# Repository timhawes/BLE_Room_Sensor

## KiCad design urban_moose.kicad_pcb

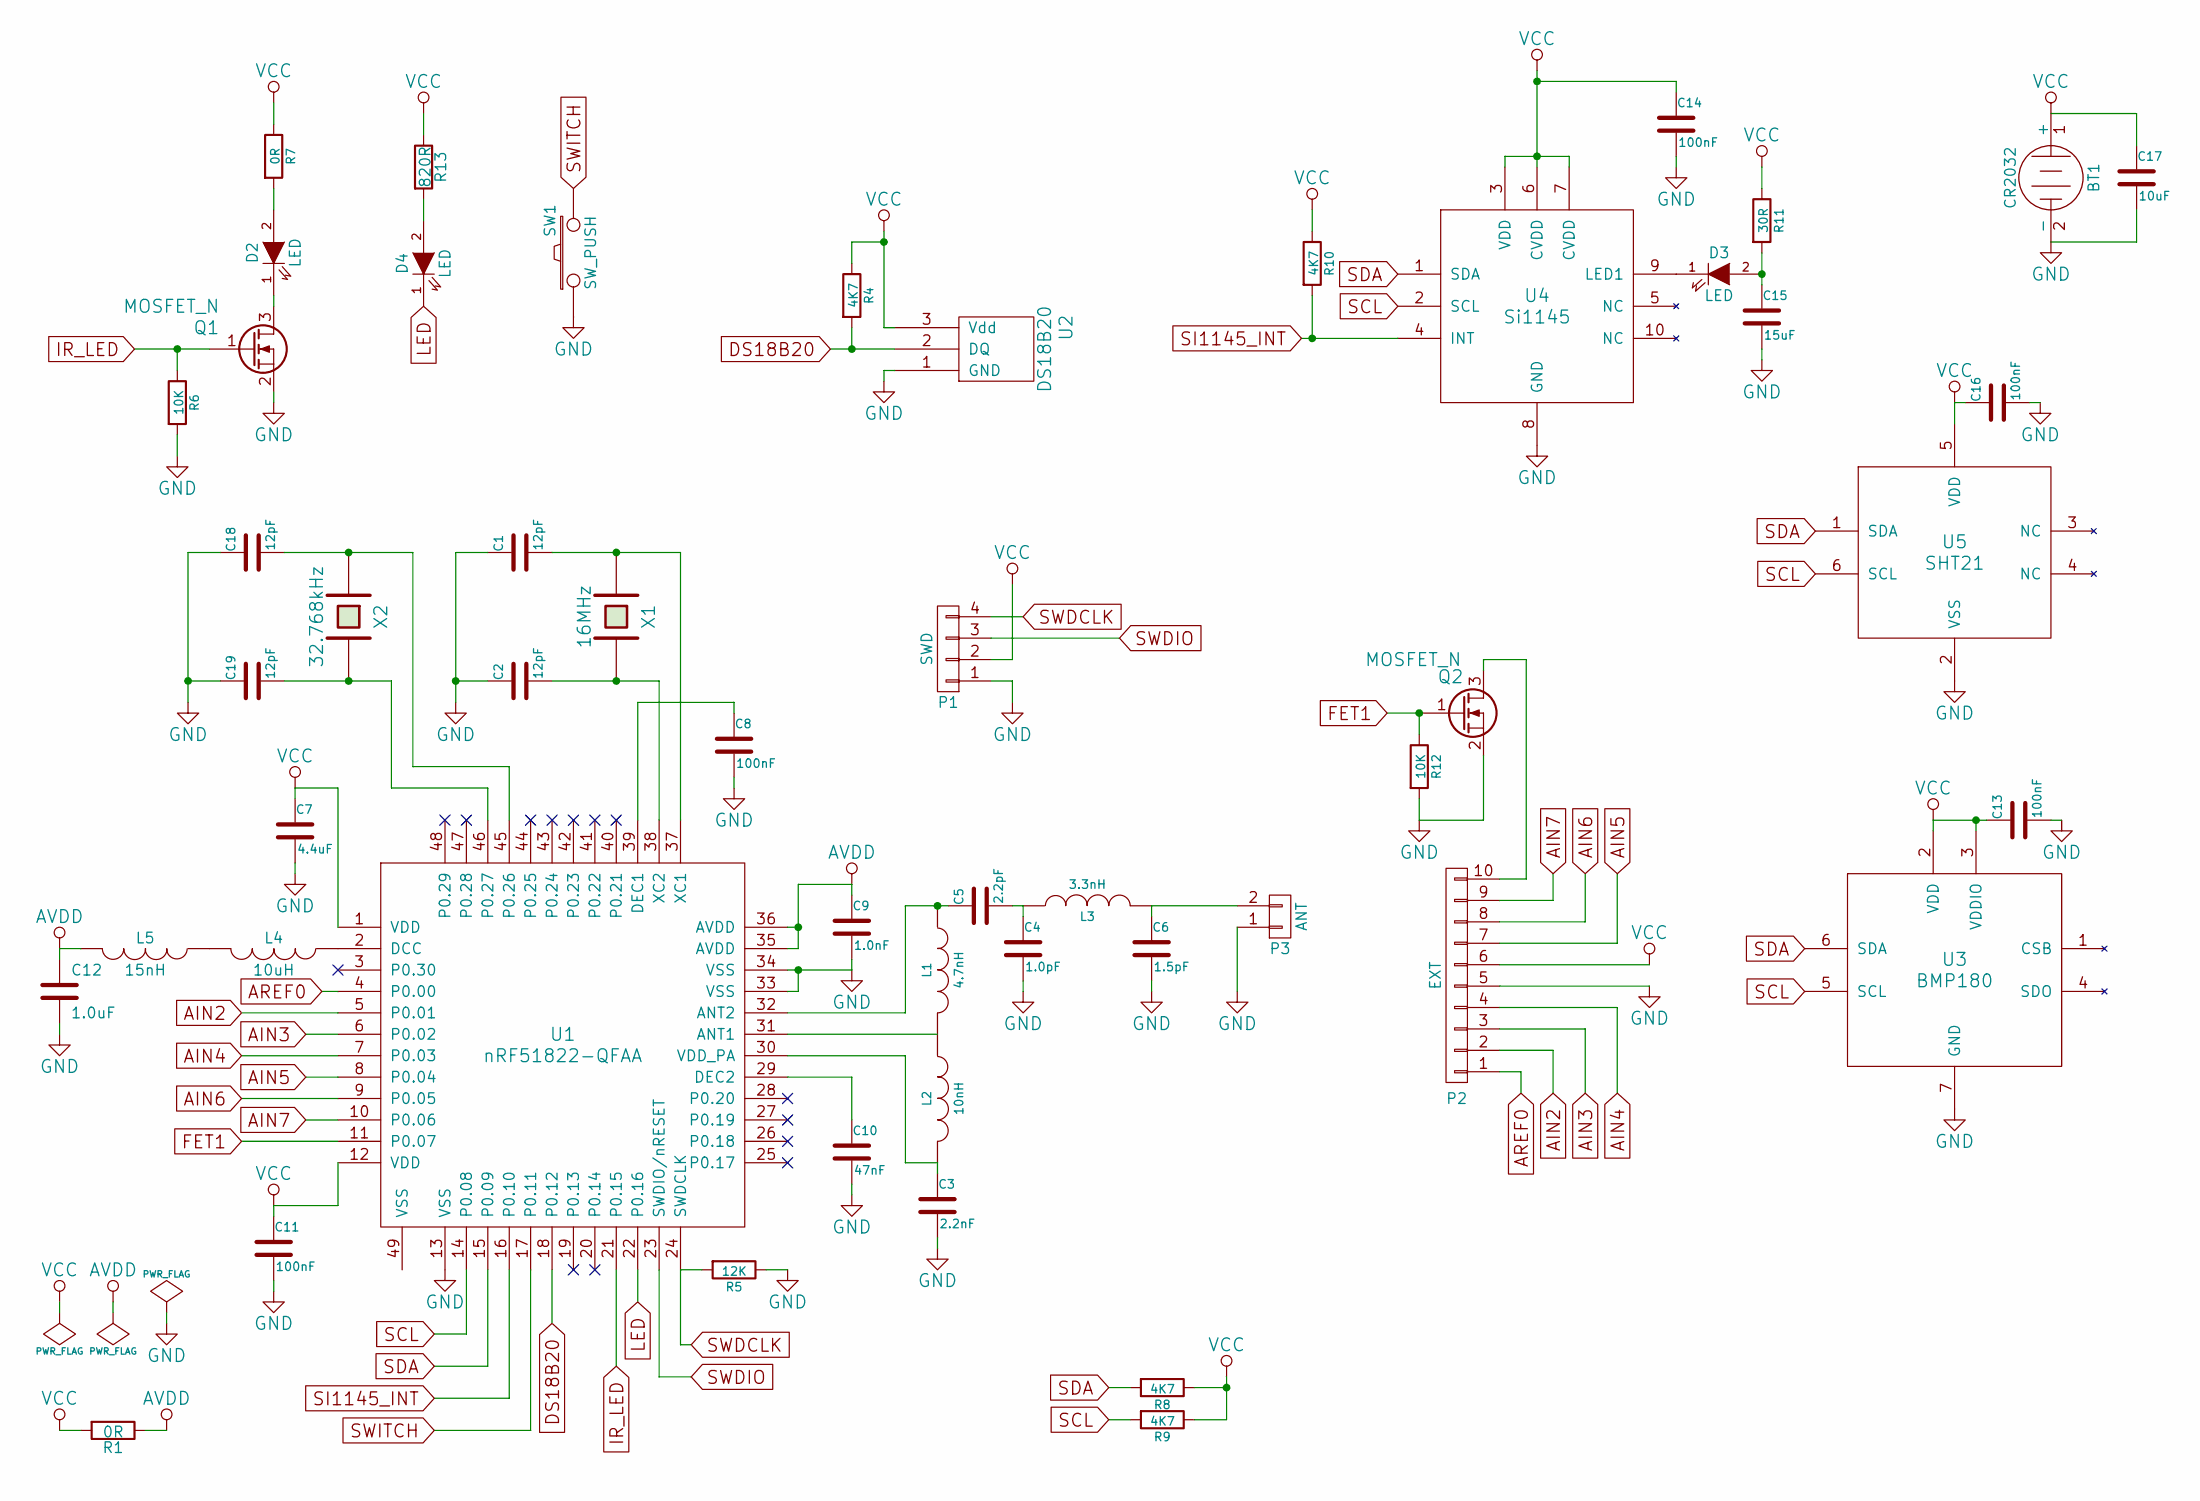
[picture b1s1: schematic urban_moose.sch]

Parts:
BT1: CR2032; BAT-HLD-001
C1, C2, C18, C19: 12pF; C_0402
C3: 2.2nF; C_0402
C4: 1.0pF; C_0402
C5: 2.2pF; C_0402
C6: 1.5pF; C_0402
C7: 4.4uF; C_0603
C8, C11, C13, C14, C16: 100nF; C_0402
C9: 1.0nF; C_0402
C10: 47nF; C_0402
C12: 1.0uF; C_0603
C15: 15uF; C_1206
C17: 10uF; C_1206
D2, D3, D4: LED; LED-0603
L1: 4.7nH; R_0402
L2: 10nH; R_0402
L3: 3.3nH; R_0402
L4: 10uH; R_0603
L5: 15nH; R_0402
P1: SWD; Pin_Header_Straight_1x04
P2: EXT; Pin_Header_Straight_1x10
P3: ANT; ANT-2.4GHz
Q1, Q2: MOSFET_N; SOT-23
R1, R7: 0R; R_0402
R4, R8, R9, R10: 4K7; R_0402
R5: 12K; R_0402
R6, R12: 10K; R_0402
R11: 30R; R_0402
R13: 820R; R_0402
SW1: SW_PUSH; EVQPT5
U1: nRF51822-QFAA; UQFN-48-1EP_6x6mm_Pitch0.4mm
U2: DS18B20; Pin_Header_Straight_1x03
U3: BMP180
U4: Si1145; Si114x
U5: SHT21
X1: 16MHz; CX2520DB
X2: 32.768kHz; FC-135

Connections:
AIN2: P2.2, U1.5 (P0.01)
AIN3: P2.3, U1.6 (P0.02)
AIN4: P2.4, U1.7 (P0.03)
AIN5: P2.7, U1.8 (P0.04)
AIN6: P2.8, U1.9 (P0.05)
AIN7: P2.9, U1.10 (P0.06)
AREF0: P2.1, U1.4 (P0.00)
AVDD: C9.1, C12.1, L5.2, R1.1, U1.35 (AVDD), U1.36 (AVDD)
DS18B20: R4.2, U1.18 (P0.12), U2.2 (DQ)
FET1: Q2.1 (G), R12.1, U1.11 (P0.07)
GND: BT1.2 (-), C1.1, C2.1, C3.2, C4.2, C6.2, C7.2, C8.2, C9.2, C10.2, C11.2, C12.2, C13.2, C14.2, C15.2, C16.2, C17.2, C18.1, C19.1, P1.1, P2.5, P3.1, Q1.2 (S), Q2.2 (S), R5.1, R6.2, R12.2, SW1.1, U1.13 (VSS), U1.33 (VSS), U1.34 (VSS), U1.49 (VSS), U2.1 (GND), U3.7 (GND), U4.8 (GND), U5.2 (VSS)
IR_LED: Q1.1 (G), R6.1, U1.21 (P0.15)
LED: D4.1 (K), U1.22 (P0.16)
unnamed: C1.2, U1.37 (XC1), X1.1
unnamed: C2.2, U1.38 (XC2), X1.2
unnamed: C3.1, L2.2, U1.30 (VDD_PA)
unnamed: C4.1, C5.2, L3.1
unnamed: C5.1, L1.1, U1.32 (ANT2)
unnamed: C6.1, L3.2, P3.2
unnamed: C8.1, U1.39 (DEC1)
unnamed: C10.1, U1.29 (DEC2)
unnamed: C15.1, D3.2 (A), R11.2
unnamed: C18.2, U1.45 (P0.26), X2.1
unnamed: C19.2, U1.46 (P0.27), X2.2
unnamed: D2.1 (K), Q1.3 (D)
unnamed: D2.2 (A), R7.2
unnamed: D3.1 (K), U4.9 (LED1)
unnamed: D4.2 (A), R13.2
unnamed: L1.2, L2.1, U1.31 (ANT1)
unnamed: L4.1, U1.2 (DCC)
unnamed: L4.2, L5.1
unnamed: P2.10, Q2.3 (D)
SCL: R9.2, U1.14 (P0.08), U3.5 (SCL), U4.2 (SCL), U5.6 (SCL)
SDA: R8.2, U1.15 (P0.09), U3.6 (SDA), U4.1 (SDA), U5.1 (SDA)
SI1145_INT: R10.2, U1.16 (P0.10), U4.4 (INT)
SWDCLK: P1.4, R5.2, U1.24 (SWDCLK)
SWDIO: P1.3, U1.23 (SWDIO/nRESET)
SWITCH: SW1.2, U1.17 (P0.11)
VCC: BT1.1 (+), C7.1, C11.1, C13.1, C14.1, C16.1, C17.1, P1.2, P2.6, R1.2, R4.1, R7.1, R8.1, R9.1, R10.1, R11.1, R13.1, U1.1 (VDD), U1.12 (VDD), U2.3 (Vdd), U3.2 (VDD), U3.3 (VDDIO), U4.3 (VDD), U4.6 (CVDD), U4.7 (CVDD), U5.5 (VDD)

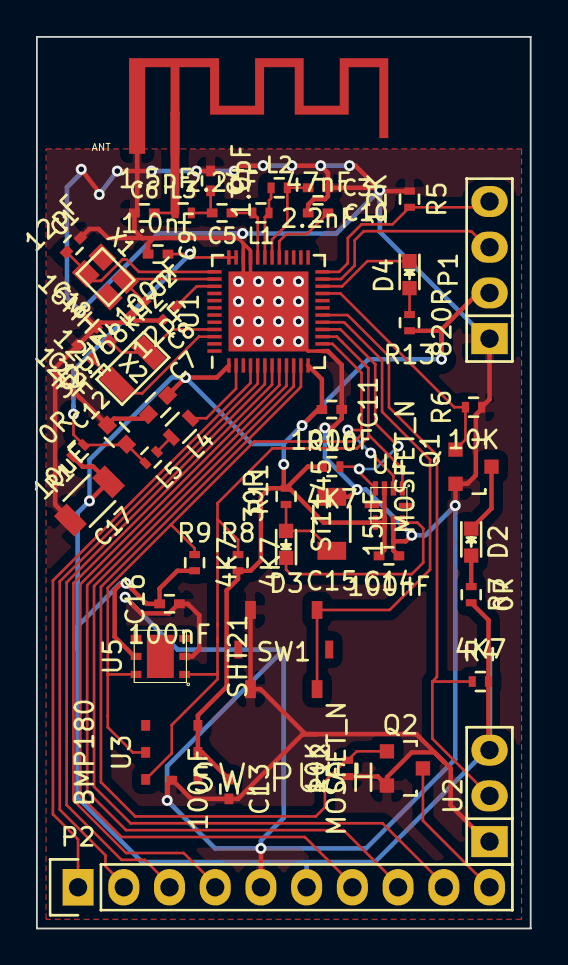
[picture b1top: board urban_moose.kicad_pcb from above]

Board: 2 copper layers, 27.4 x 49.5 mm, 52 parts (1 on the bottom side), 39 nets.

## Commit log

2015-01-15 Initial commit.
2015-01-17 Multiple changes.
    DC/DC mode support
    LF crystal support
    RGB LED replaced with simple LED
2015-05-24 Many rolled-up changes
2015-05-24 Project renamed
2015-05-24 Ground vias added near matching components
2015-05-30 Tidy-ups
2015-05-30 Gerbers generated
2015-05-30 Move antenna away from ground plane
2015-05-31 Made some references smaller. Generated paste layers.
2015-06-10 Remove paste from battery contact
2015-06-10 .gitignore file added
2015-06-10 Gerbers regenerated, and new file extensions used
2015-11-04 Fixes to match library changes
2015-11-04 Change footprint for nRF51 to the correct pitch
2015-11-04 Restore ground plane to previous commit
2015-11-04 Update schematic PDF
2015-11-04 Update URL text to um2
2015-11-04 Additional via stitching, track tidy-ups
2015-11-04 Connect nRF51 centre pad and add vias
2015-11-04 Routing tidy-up
2015-11-04 Tidy-up ground pins on nRF51 and replace LED silkscreens
2015-11-04 Reposition D3 label
